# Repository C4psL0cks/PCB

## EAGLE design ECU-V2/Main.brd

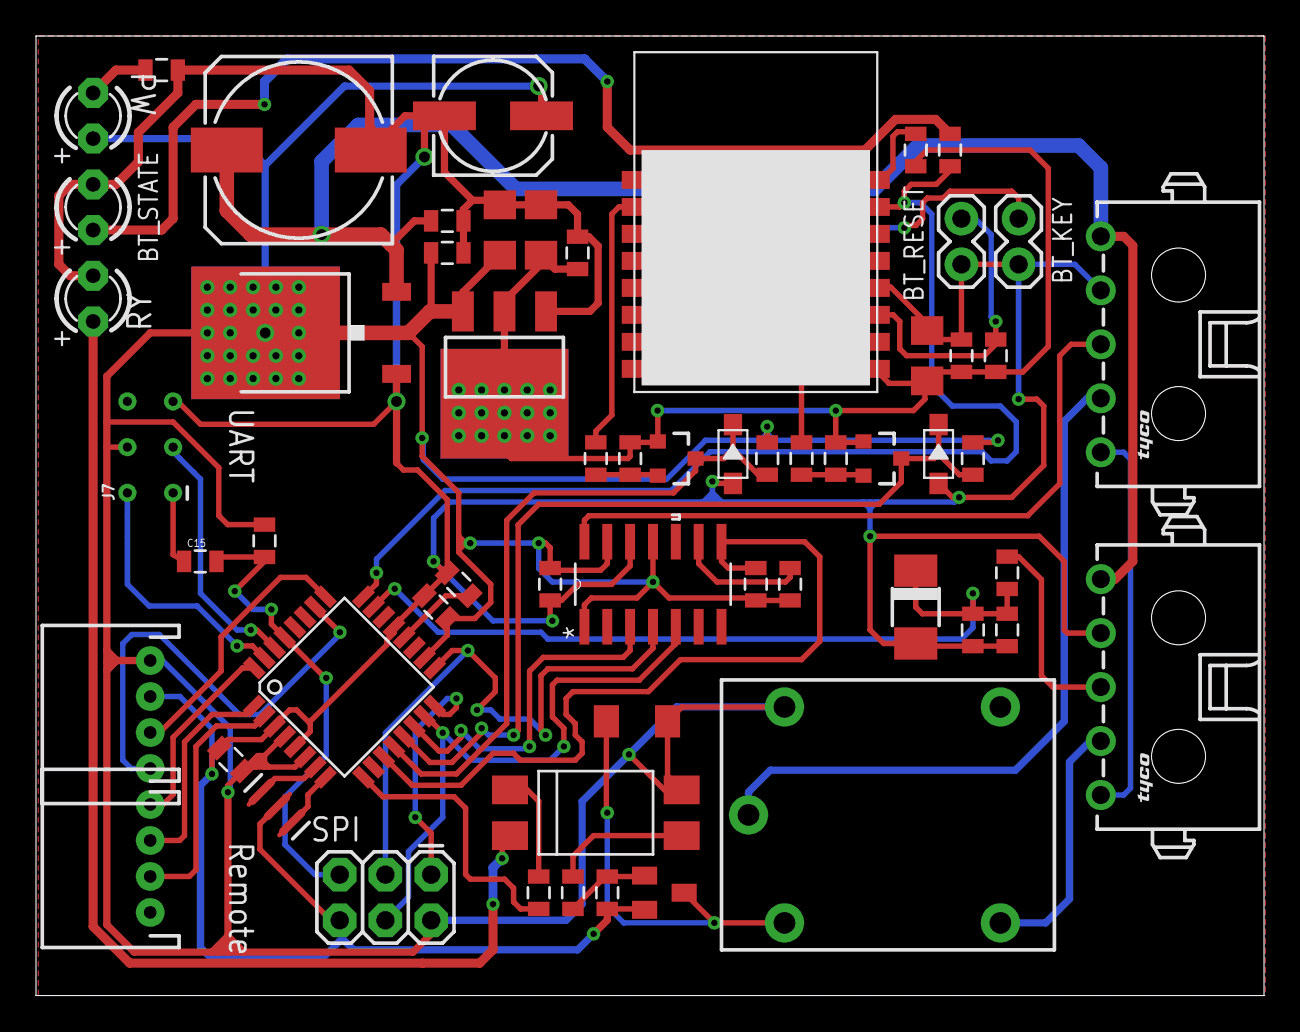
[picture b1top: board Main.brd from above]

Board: 2 copper layers, 68.2 x 53.3 mm, 59 parts (0 on the bottom side), 45 nets.

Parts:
C1, C3, C6, C7, C12, C13, C14, C15: 0.1uF; 0805
C2: 10uF; C1206
C4: 22uF; C1206
C5: 4.7uF; C1206
C9, C18: 0.1; 0805
C10: 220/50; 153CLV-1010
C11: 100/35; 153CLV-0605
D1, D2: SMF5.0A; SOD123-2.7X1.6
D4: SZ105B; DO-214AC
D12: 4148; SOD80
IC1: MEGA8-AI; TQFP32-08
IC2: LM1117DTX-5.0; TO252
J1, J3: CP3505P1H00-S-LF; 1445055-5
J4: SPI; 2X3
J5: JST-4-PTH
J6: Remote; JST-4-PTH
J7: AVR_SPI_PROG_3X2TESTPOINTS; 2X3_TEST_POINTS
JP1: BT_RESET; 1X02
JP2: BT_KEY; 1X02
LED1: BT_STATE; LED3MM
LED2: PW; LED3MM
LED3: RY; LED3MM
OK1: PC817; DIL4-SMD
Q3, Q4: BSS138BK; SOT23-3
R1, R2, R3, R4, R8, R9, R10, R11: 10k; 0805
R5, R6, R7, R14, R16, R17: 1k; 0805
R12: 330; 0805
R13: 4.7k; 0805
R15: 2.2k; 0805
R18: 3.9k; 0805
T3: BC817; SOT23-BEC
U1: MCP4922-E/SL; SOIC127P600X175-14N
U2: HM-11; 16P-18.5X13.5X0.8
U4: LM1117 3.3; SOT223
U$10: RELAYPTH; SRD-05VDC-SL-C
Y1: 16MHZ; RESONATOR-SMD

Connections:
3.3V: C1.1, C2.1, C3.1, C4.1, Q3.1, Q4.1, R1.2, R3.2, R8.1, R16.1, U2.9, U4.2, U4.4
12V: C10.+, C12.1, IC2.2, J1.1, J3.1
A0: C18.1, D4.C, IC1.23, R13.1, R15.2
A1: IC1.24, R6.2, U2.15
A2: IC1.25, J5.2
A3: IC1.26, J5.1
CS: IC1.14, U1.3
D2: IC1.32, J6.4
D3: IC1.1, J6.3
D4: IC1.2, J6.2
D5: IC1.9, R12.1
D7: IC1.11, R11.1, U1.8
D8: D2.2, IC1.12, Q3.3, R2.1
D9: D1.2, IC1.13, Q4.3, R4.1
GND: C1.2, C2.2, C3.2, C4.2, C5.2, C6.1, C7.1, C9.2, C10.-, C11.-, C12.2, C13.2, C14.2, C18.2, D1.1, D2.1, D4.A, IC1.3, IC1.5, IC1.21, IC2.1, J1.2, J3.2, J4.6, J5.3, J7.5, JP1.2, JP2.2, LED1.K, LED3.K, R14.2, R15.1, R18.1, T3.E, U1.12, U2.12, U4.1, Y1.2
MISO: IC1.16, J4.1
MOSI: IC1.15, J4.4, U1.5
unnamed: LED1.A, R6.1
unnamed: JP2.1, R16.2, U2.16
unnamed: R5.1, U2.2
unnamed: JP1.1, R8.2, U2.11
unnamed: IC1.8, Y1.3
unnamed: R7.1, U2.4
unnamed: IC1.7, Y1.1
unnamed: C7.2, IC1.20
unnamed: J3.4, U$10.SWCOMMON
unnamed: LED2.K, R14.1
unnamed: J3.3, U1.14
unnamed: J1.5, J3.5
unnamed: J1.4, U$10.SWCLOSED
unnamed: R10.1, U1.9
unnamed: C15.1, J7.1
unnamed: OK1.3, R17.1
unnamed: R17.2, R18.2, T3.B
unnamed: D12.2, T3.C, U$10.COIL0
unnamed: OK1.1, R12.2
unnamed: LED3.A, OK1.2
RST: C15.2, IC1.29, J4.5, R9.1
RXD: IC1.30, J7.3
RXD1: Q4.2, R3.1, R7.2
SCK: IC1.17, J4.3, U1.4
SENS_IN: J1.3, R13.2
TXD: IC1.31, J7.2
TXD1: Q3.2, R1.1, R5.2
VCC: C5.1, C6.2, C9.1, C11.+, C13.1, C14.1, D12.1, IC1.4, IC1.6, IC1.18, IC2.TAB, J4.2, J5.4, J7.4, LED2.A, OK1.4, R2.2, R4.2, R9.2, R10.2, R11.2, U1.1, U1.11, U1.13, U4.3, U$10.COIL1

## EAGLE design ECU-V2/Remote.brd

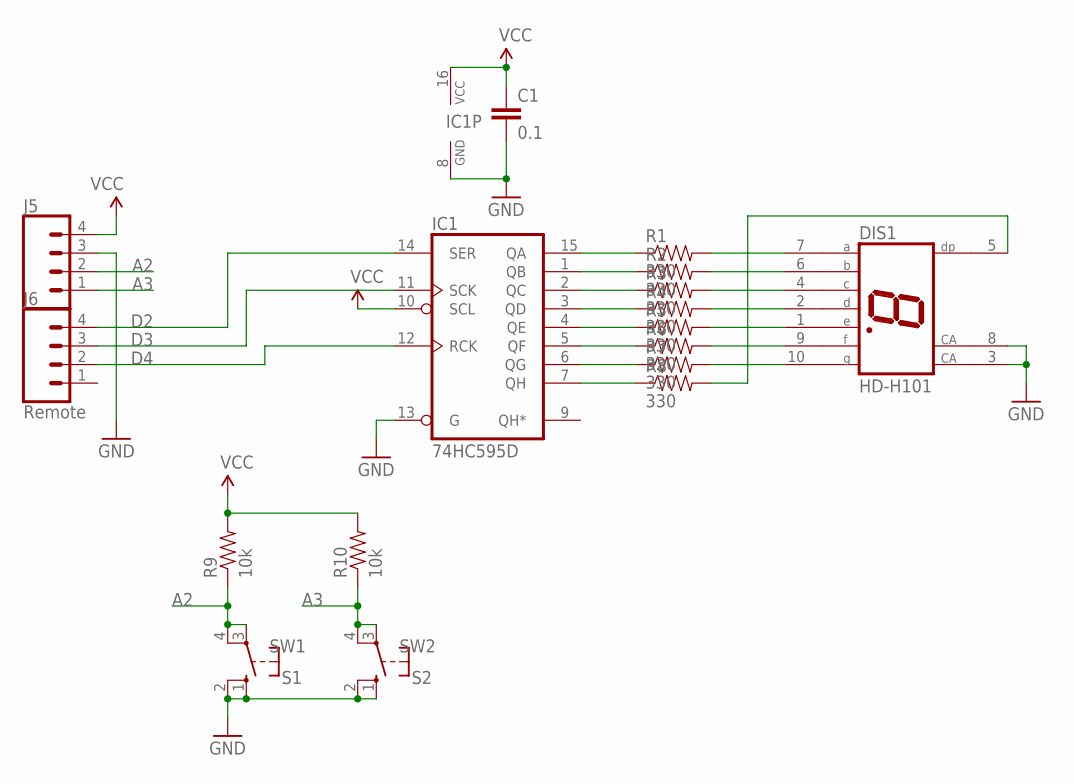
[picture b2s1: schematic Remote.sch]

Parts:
C1: 0.1; 0805
DIS1: HD-H101; HDSP-M
IC1: 74HC595D; SO16
J5: CONN_04JST-PTH; JST-4-PTH
J6: Remote; JST-4-PTH
R1, R2, R3, R4, R5, R6, R7, R8: 330; 0805
R9, R10: 10k; 0805
S1: SW1; B3F-10XX; MPN B3F-1000
S2: SW2; B3F-10XX; MPN B3F-1000

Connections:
A2: J5.2, R9.1, S1.3, S1.4 (P1)
A3: J5.1, R10.1, S2.3, S2.4 (P1)
D2: IC1.14 (SER), J6.4
D3: IC1.11 (SCK), J6.3
D4: IC1.12 (RCK), J6.2
GND: C1.2, DIS1.3 (CA), DIS1.8 (CA), IC1.8 (GND), IC1.13 (G), J5.3, S1.1 (S), S1.2 (S1), S2.1 (S), S2.2 (S1)
unnamed: IC1.15 (QA), R1.1
unnamed: IC1.1 (QB), R2.1
unnamed: DIS1.5 (DP), R8.2
unnamed: IC1.2 (QC), R3.1
unnamed: IC1.3 (QD), R4.1
unnamed: IC1.4 (QE), R5.1
unnamed: IC1.5 (QF), R6.1
unnamed: IC1.6 (QG), R7.1
unnamed: IC1.7 (QH), R8.1
unnamed: DIS1.7 (A), R1.2
unnamed: DIS1.6 (B), R2.2
unnamed: DIS1.4 (C), R3.2
unnamed: DIS1.2 (D), R4.2
unnamed: DIS1.1 (E), R5.2
unnamed: DIS1.9 (F), R6.2
unnamed: DIS1.10 (G), R7.2
VCC: C1.1, IC1.10 (SCL), IC1.16 (VCC), J5.4, R9.2, R10.2

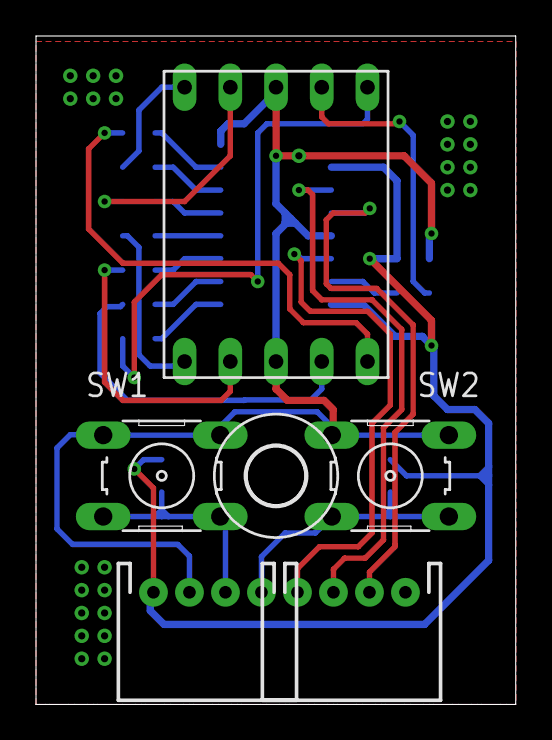
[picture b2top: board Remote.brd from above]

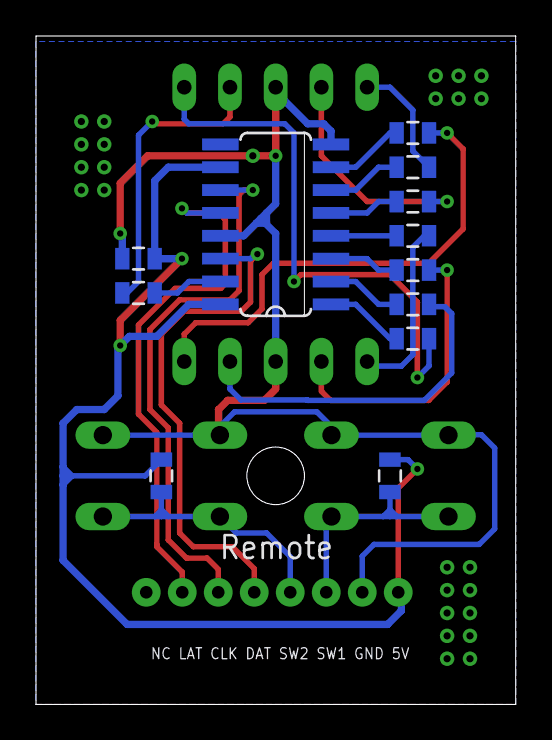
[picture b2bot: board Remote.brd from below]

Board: 2 copper layers, 26.7 x 37.1 mm, 18 parts (12 on the bottom side), 23 nets.

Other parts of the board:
U$1: 3,2

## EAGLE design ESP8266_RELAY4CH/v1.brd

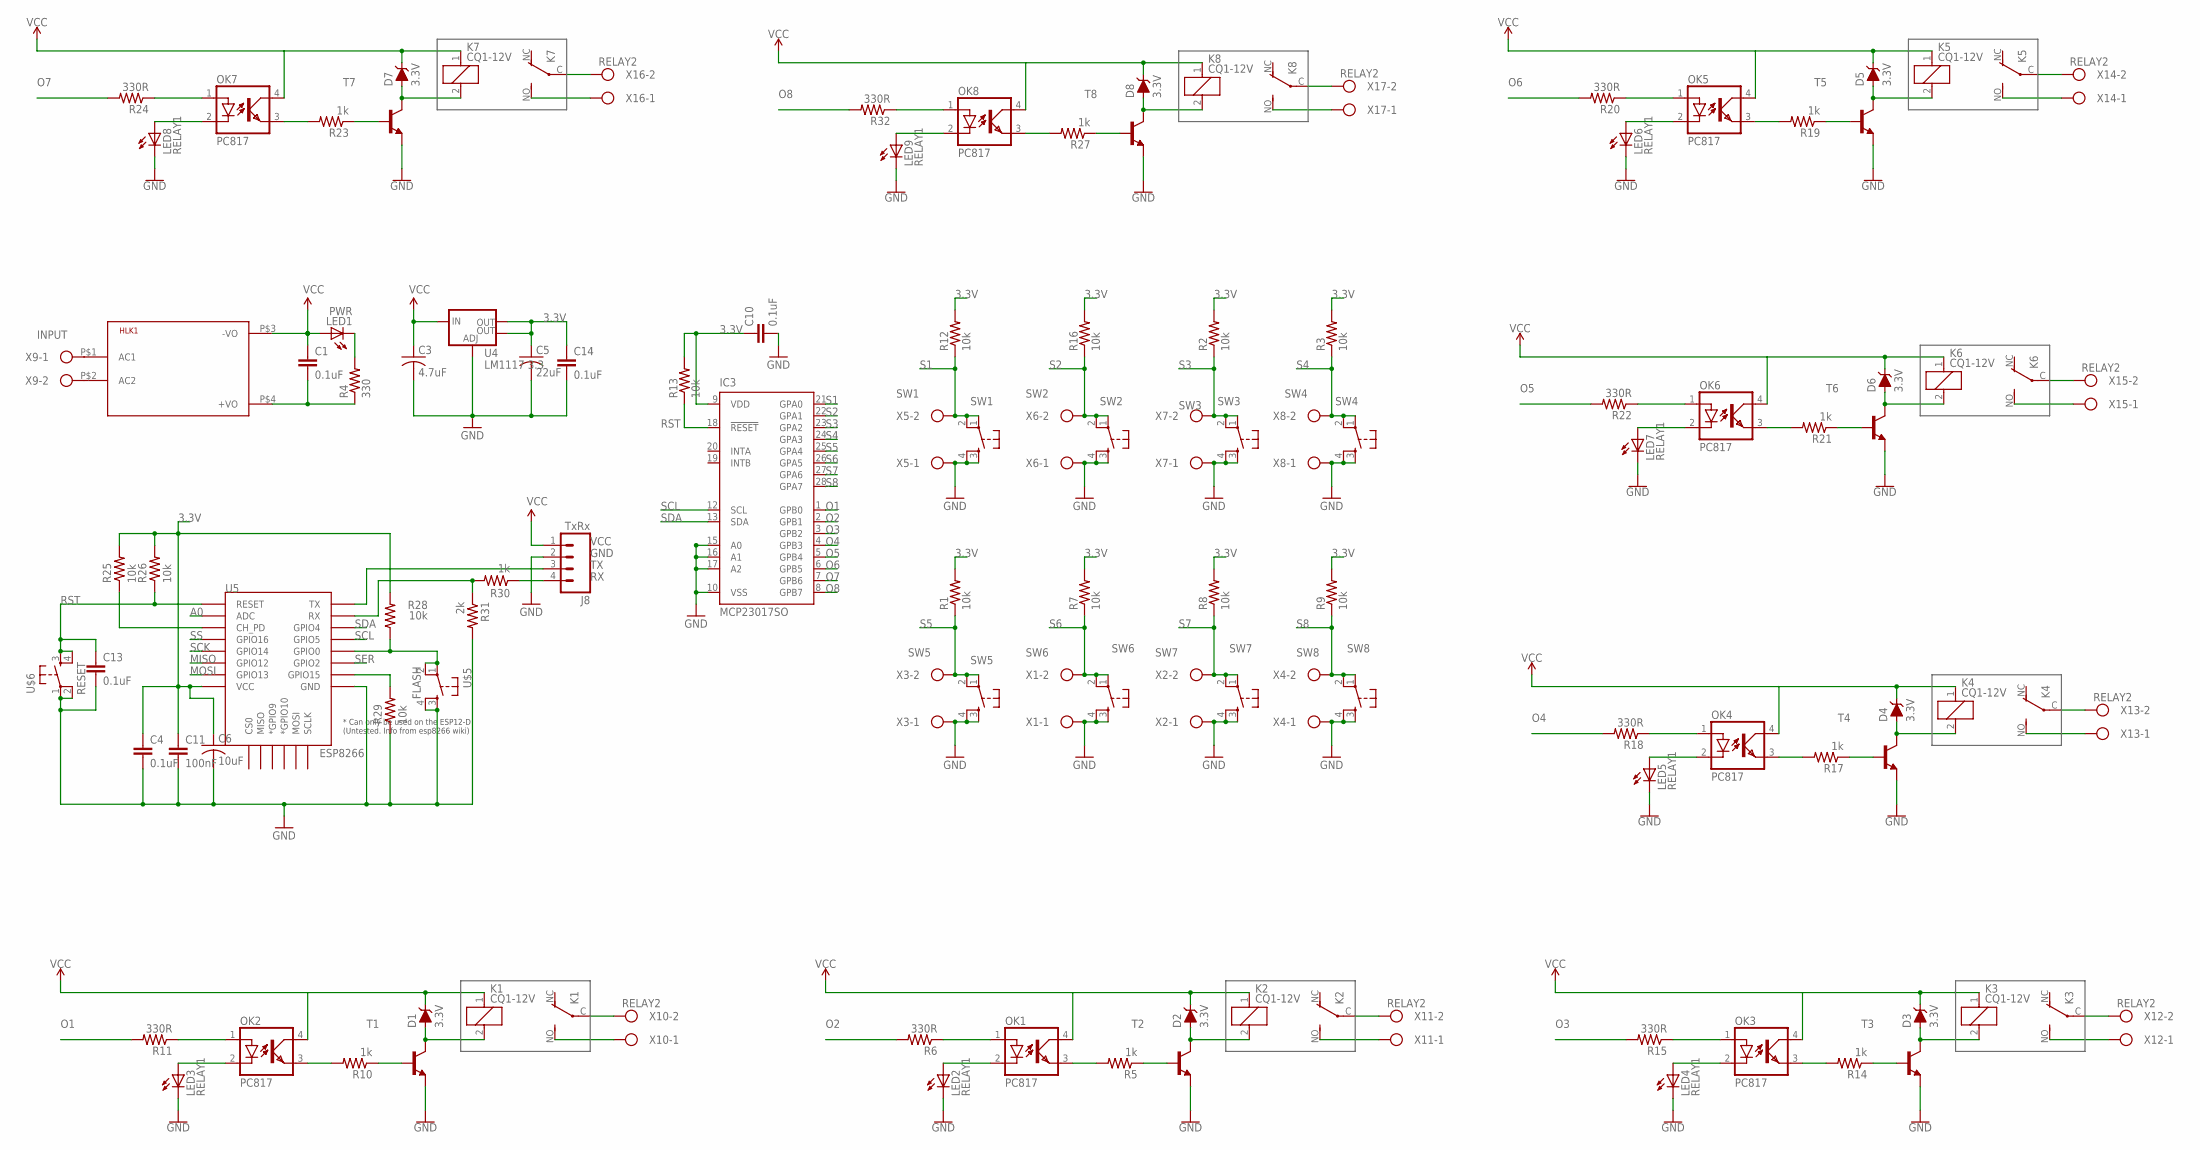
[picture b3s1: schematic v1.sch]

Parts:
C1, C4, C10, C13, C14: 0.1uF; 0805
C3: 4.7uF; C1206
C5: 22uF; C1206
C6: 10uF; C1206
C11: 100nF; 0805
D1, D2, D3, D4, D5, D6, D7, D8: 3.3V; SOD-323
HLK1: HLK-PM013W; HLK-PM01
IC3: MCP23017SO; SO28W
J8: TxRx; MOLEX-1X4
K1, K2, K3, K4, K5, K6, K7, K8: CQ1-12V; CQ1
LED1: PWR; CHIP-LED0805
LED2, LED3, LED4, LED5, LED6, LED7, LED8, LED9: RELAY1; CHIP-LED0805
OK1, OK2, OK3, OK4, OK5, OK6, OK7, OK8: PC817; DIL04
R1, R2, R3, R7, R8, R9, R12, R13, R16, R25, R26, R28, R29: 10k; 0805
R4: 330; 0805
R5, R10, R14, R17, R19, R21, R23, R27, R30: 1k; 0805
R6, R11, R15, R18, R20, R22, R24, R32: 330R; 0805
R31: 2k; 0805
T1, T2, T3, T4, T5, T6, T7, T8: -NPN-SOT23-BEC; SOT23-BEC
U4: LM1117 3.3; SOT223
U5: ESP8266; ESP12E-SMD
U$1: SW1; TAC-SWITCH-PTH
U$2: SW2; TAC-SWITCH-PTH
U$3: SW5; TAC-SWITCH-PTH
U$4: SW3; TAC-SWITCH-PTH
U$5: FLASH; TAC-SWITCH-PTH
U$6: RESET; TAC-SWITCH-PTH
U$7: SW4; TAC-SWITCH-PTH
U$8: SW6; TAC-SWITCH-PTH
U$9: SW7; TAC-SWITCH-PTH
U$10: SW8; TAC-SWITCH-PTH
X1: SW6; W237-102
X2: SW7; W237-102
X3: SW5; W237-102
X4: SW8; W237-102
X5: SW1; W237-102
X6: SW2; W237-102
X7: SW3; W237-102
X8: SW4; W237-102
X9: INPUT; W237-102
X10, X11, X12, X13, X14, X15, X16, X17: RELAY2; W237-102

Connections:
1: D2.A, K2.2, T2.C
2: D3.A, K3.2, T3.C
3: D4.A, K4.2, T4.C
3.3V: C4.1, C5.1, C6.1, C10.1, C11.1, C14.1, IC3.9 (VDD), R1.2, R2.2, R3.2, R7.2, R8.2, R9.2, R12.2, R13.2, R16.2, R25.2, R26.2, R28.2, U4.2 (OUT), U4.4 (OUT), U5.VCC
4: D5.A, K5.2, T5.C
5: D6.A, K6.2, T6.C
6: D7.A, K7.2, T7.C
7: D8.A, K8.2, T8.C
22: D1.A, K1.2, T1.C
A0: U5.ADC
GND: C3.2, C4.2, C5.2, C6.2, C10.2, C11.2, C13.2, C14.2, IC3.10 (VSS), IC3.15 (A0), IC3.16 (A1), IC3.17 (A2), J8.2, LED2.C, LED3.C, LED4.C, LED5.C, LED6.C, LED7.C, LED8.C, LED9.C, R29.1, R31.2, T1.E, T2.E, T3.E, T4.E, T5.E, T6.E, T7.E, T8.E, U4.1 (ADJ), U5.GND, U$1.3, U$1.4, U$2.3, U$2.4, U$3.3, U$3.4, U$4.3, U$4.4, U$5.3, U$5.4, U$6.1, U$6.2, U$7.3, U$7.4, U$8.3, U$8.4, U$9.3, U$9.4, U$10.3, U$10.4, X1.1, X2.1, X3.1, X4.1, X5.1, X6.1, X7.1, X8.1
INSS: OK2.1 (A), R11.1
INSS1: OK1.1 (A), R6.1
INSS2: OK3.1 (A), R15.1
INSS3: OK4.1 (A), R18.1
INSS4: OK5.1 (A), R20.1
INSS5: OK6.1 (A), R22.1
INSS6: OK7.1 (A), R24.1
INSS7: OK8.1 (A), R32.1
LEDS: LED3.A, OK2.2 (C)
LEDS1: LED2.A, OK1.2 (C)
LEDS2: LED4.A, OK3.2 (C)
LEDS3: LED5.A, OK4.2 (C)
LEDS4: LED6.A, OK5.2 (C)
LEDS5: LED7.A, OK6.2 (C)
LEDS6: LED8.A, OK7.2 (C)
LEDS7: LED9.A, OK8.2 (C)
MISO: U5.GPIO12
MOSI: U5.GPIO13
unnamed: C1.2, HLK1.P$4 (+VO), R4.1
unnamed: HLK1.P$1 (AC1), X9.1
unnamed: HLK1.P$2 (AC2), X9.2
unnamed: K1.NO (S), X10.1
unnamed: K1.C, X10.2
unnamed: R5.1, T2.B
unnamed: OK1.3 (EMIT), R5.2
unnamed: K2.NO (S), X11.1
unnamed: LED1.C, R4.2
unnamed: K2.C, X11.2
unnamed: R14.1, T3.B
unnamed: OK3.3 (EMIT), R14.2
unnamed: K3.NO (S), X12.1
unnamed: K3.C, X12.2
unnamed: R17.1, T4.B
unnamed: OK4.3 (EMIT), R17.2
unnamed: K4.NO (S), X13.1
unnamed: K4.C, X13.2
unnamed: R19.1, T5.B
unnamed: R10.1, T1.B
unnamed: OK5.3 (EMIT), R19.2
unnamed: OK2.3 (EMIT), R10.2
unnamed: K5.NO (S), X14.1
unnamed: K5.C, X14.2
unnamed: R21.1, T6.B
unnamed: R30.2, R31.1, U5.RXD0 (RX)
unnamed: OK6.3 (EMIT), R21.2
unnamed: K6.NO (S), X15.1
unnamed: K6.C, X15.2
unnamed: R23.1, T7.B
unnamed: OK7.3 (EMIT), R23.2
unnamed: K7.NO (S), X16.1
unnamed: K7.C, X16.2
unnamed: R27.1, T8.B
unnamed: OK8.3 (EMIT), R27.2
unnamed: R25.1, U5.CH_PD
unnamed: R28.1, U5.GPIO0, U$5.1, U$5.2
unnamed: R29.2, U5.GPIO15
unnamed: K8.NO (S), X17.1
unnamed: K8.C, X17.2
O1: IC3.1 (GPB0), R11.2
O2: IC3.2 (GPB1), R6.2
O3: IC3.3 (GPB2), R15.2
O4: IC3.4 (GPB3), R18.2
O5: IC3.5 (GPB4), R22.2
O6: IC3.6 (GPB5), R20.2
O7: IC3.7 (GPB6), R24.2
O8: IC3.8 (GPB7), R32.2
RST: C13.1, IC3.18 (!RESET), R13.1, R26.1, U5.RESET, U$6.3, U$6.4
RX: J8.4, R30.1
S1: IC3.21 (GPA0), R12.1, U$1.1, U$1.2, X5.2
S2: IC3.22 (GPA1), R16.1, U$2.1, U$2.2, X6.2
S3: IC3.23 (GPA2), R2.1, U$4.1, U$4.2, X7.2
S4: IC3.24 (GPA3), R3.1, U$7.1, U$7.2, X8.2
S5: IC3.25 (GPA4), R1.1, U$3.1, U$3.2, X3.2
S6: IC3.26 (GPA5), R7.1, U$8.1, U$8.2, X1.2
S7: IC3.27 (GPA6), R8.1, U$9.1, U$9.2, X2.2
S8: IC3.28 (GPA7), R9.1, U$10.1, U$10.2, X4.2
SCK: U5.GPIO14
SCL: IC3.12 (SCL), U5.GPIO5
SDA: IC3.13 (SDA), U5.GPIO4
SER: U5.GPIO2
SS: U5.GPIO16
TX: J8.3, U5.TXD0 (TX)
VCC: C1.1, C3.1, D1.C, D2.C, D3.C, D4.C, D5.C, D6.C, D7.C, D8.C, HLK1.P$3 (-VO), J8.1, K1.1, K2.1, K3.1, K4.1, K5.1, K6.1, K7.1, K8.1, LED1.A, OK1.4 (COL), OK2.4 (COL), OK3.4 (COL), OK4.4 (COL), OK5.4 (COL), OK6.4 (COL), OK7.4 (COL), OK8.4 (COL), U4.3 (IN)

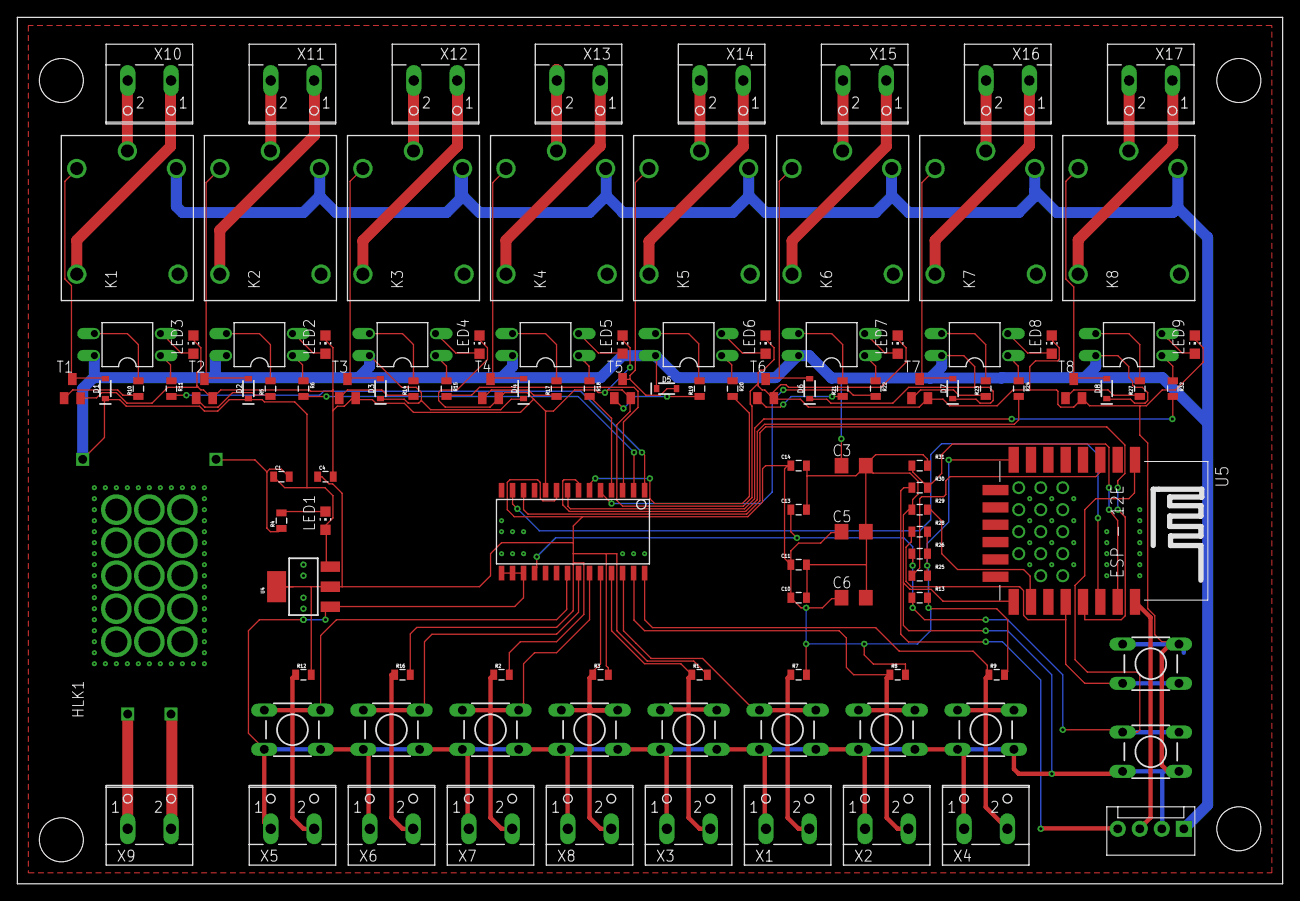
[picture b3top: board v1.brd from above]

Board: 2 copper layers, 146.0 x 100.0 mm, 114 parts (0 on the bottom side), 88 nets.

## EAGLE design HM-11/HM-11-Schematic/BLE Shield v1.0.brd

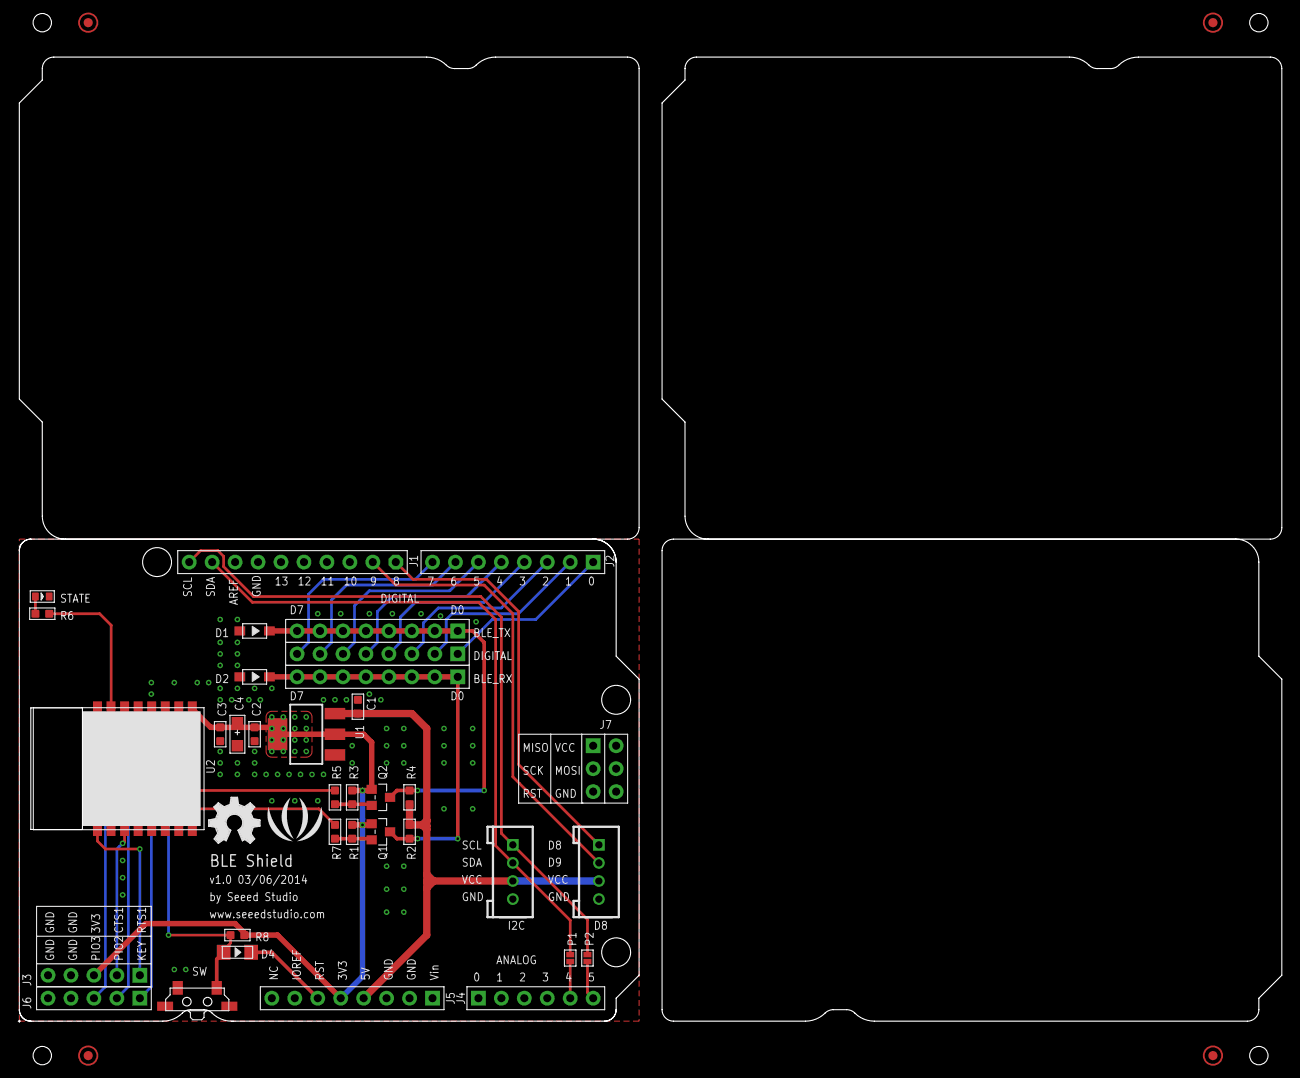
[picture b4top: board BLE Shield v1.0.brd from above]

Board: 2 copper layers, 139.8 x 106.8 mm, 41 parts (0 on the bottom side), 32 nets.

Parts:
BLE_RX: 2.54-8p-male; 8P-2.54
BLE_TX: 2.54-8p-male; 8P-2.54
C1, C2: 1uF; C0603
C3: 100nF; C0603
C4: 47uF/10v; AVX-A
D1, D2: 6.2V/250mW; SOD123-2.7X1.6
D4: 1N4148; LL-34
D8: DIP Grove; 4P-2.0
DIGITAL: 2.54-8p-male; 8P-2.54
I2C: DIP Grove; 4P-2.0
J1: DIP Long Blue Female Header; 10P-2.54
J2, J5: DIP Long Blue Female Header; 8P-2.54-65/35MIL
J3, J6: DNP; 5P-2.54
J4: DIP Long Blue Female Header; 6P-2.54-65/35MIL
J7: DIP Long Blue Female Header; 2X3P-2.54-65/35MIL
P1, P2: DNP; 2P-SMD-1.78X1.27
P3, P4, P5, P6: ROUND-MARK-1.0
Q1, Q2: 2n7002; SOT23
R1, R2, R3, R4, R8: 10k; R0603
R5, R6, R7: 1k; R0603
STATE: Green; LED-0603
SW: TS-1188E; 4P-SMD-7X3.5X3.5H
U1: CJ1117-3.3-1310190P1; SOT223
U2: HM-11; 16P-18.5X13.5X0.8
U$23: OSHW_FILLX200_NOTEXT
U$24: LOGO_SILK

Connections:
3V3: C2.2, C3.1, C4.+, J3.3, J5.5, Q1.1, Q2.1, R1.1, R3.2, R8.1, U1.2, U1.TER, U2.9
5V: C1.2, D8.3, I2C.3, J5.4, R2.2, R4.2, U1.3
A4: J4.5, P1.1
A5: J4.6, P2.1
BT_RX: BLE_RX.1, BLE_RX.2, BLE_RX.3, BLE_RX.4, BLE_RX.5, BLE_RX.6, BLE_RX.7, BLE_RX.8, D2.2, Q1.3, R2.1
BT_TX: BLE_TX.1, BLE_TX.2, BLE_TX.3, BLE_TX.4, BLE_TX.5, BLE_TX.6, BLE_TX.7, BLE_TX.8, D1.2, Q2.3, R4.1
CTS1: J3.2, U2.3
D0: DIGITAL.1, J2.1
D1: DIGITAL.2, J2.2
D2: DIGITAL.3, J2.3
D3: DIGITAL.4, J2.4
D4: DIGITAL.5, J2.5
D5: DIGITAL.6, J2.6
D6: DIGITAL.7, J2.7
D7: DIGITAL.8, J2.8
D8: D8.1, J1.1
D9: D8.2, J1.2
GND: C1.1, C2.1, C3.2, C4.-, D1.1, D2.1, D8.4, I2C.4, J1.7, J3.4, J3.5, J5.2, J5.3, J6.4, J6.5, STATE.-, SW.1, SW.S1, SW.S2, U1.1, U2.12
KEY: J6.1, U2.16
LED: R6.1, U2.15
unnamed: R6.2, STATE.+
unnamed: R5.2, U2.2
unnamed: R7.2, U2.4
PIO2: J6.2, U2.14
PIO3: J6.3, U2.13
RESET: D4.C, J5.6
RST: D4.A, R8.2, SW.2, U2.11
RTS1: J3.1, U2.1
RXD1: Q1.2, R1.2, R7.1
SCL: I2C.1, J1.10, P2.2
SDA: I2C.2, J1.9, P1.2
TXD1: Q2.2, R3.1, R5.1

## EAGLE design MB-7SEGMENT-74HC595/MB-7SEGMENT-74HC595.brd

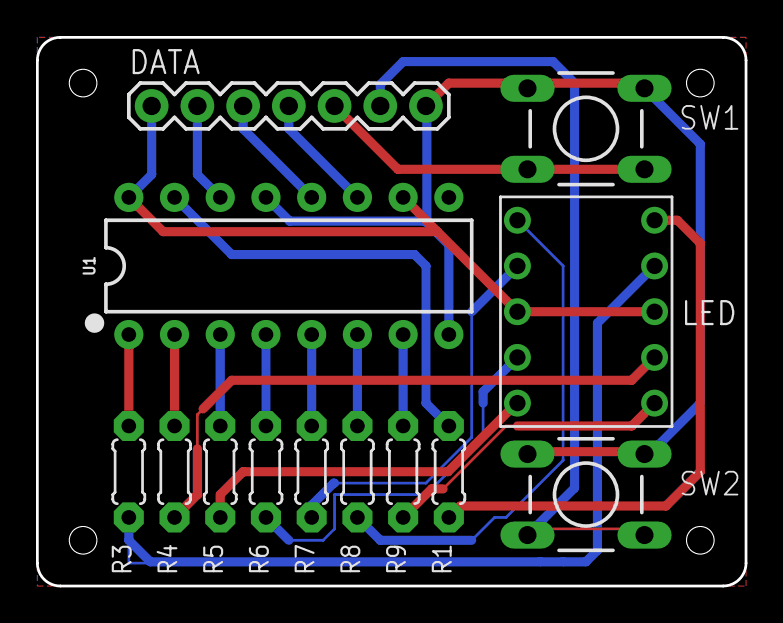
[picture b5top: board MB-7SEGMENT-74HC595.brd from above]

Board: 2 copper layers, 39.4 x 30.5 mm, 13 parts (0 on the bottom side), 23 nets.

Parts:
DATA: 1X07
LED: S4301B
R1, R3, R4, R5, R6, R7, R8, R9: 330R; 0204/5
SW1, SW2: DTS-6
U1: SN74HC595N; DIP16

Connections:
+5V: DATA.1, LED.3, LED.8, U1.10, U1.16
D4: DATA.2, U1.14
D7: DATA.3, U1.12
D8: DATA.4, U1.11
GND: DATA.7, SW1.1, SW1.2, SW2.1, SW2.2, U1.8, U1.13
unnamed: LED.10, R1.1
unnamed: LED.9, R3.1
unnamed: R1.2, U1.15
unnamed: R3.2, U1.1
unnamed: R4.2, U1.2
unnamed: R5.2, U1.3
unnamed: R6.2, U1.4
unnamed: R7.2, U1.5
unnamed: R8.2, U1.6
unnamed: R9.2, U1.7
unnamed: LED.7, R4.1
unnamed: LED.5, R5.1
unnamed: LED.4, R6.1
unnamed: LED.2, R7.1
unnamed: LED.1, R8.1
unnamed: LED.6, R9.1
SW1: DATA.5, SW1.3, SW1.4
SW2: DATA.6, SW2.3, SW2.4

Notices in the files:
parts and their libraries:
SparkFun-Connectors: Licensing: Creative Commons ShareAlike 4.0 International - https://creativecommons.org/licenses/by-sa/4.0
SparkFun: Licensing: CC v3.0 Share-Alike You are welcome to use this library for commercial purposes.
